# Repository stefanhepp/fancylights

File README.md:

FancyLights
===========

This is the sourcecode and plans for my home LED light and projector control system.

Content
=======

This project consists of the following controller boards:
- `keypad`: Sources for a keypad controller that communicates via RS232 with the main controller board and via I2C with a Raspberry PI.
- `fancycontrol`: Sources for the main light controller, which controls the lights and screen, and communicates via I2C with the projector control board.
- `projector`: Sources for the projector control board, which controls a servo for the projector mount locking mechanism and communicates via RS232 with the projector.

This repository contains the following folders:
- `kicad`: KiCAD schematics for all boards.
- `src`: Sources for all AtMega microcontrollers.

License
=======

This program is free software: you can redistribute it and/or modify
it under the terms of the GNU General Public License as published by
the Free Software Foundation, either version 3 of the License, or
(at your option) any later version.

This program is distributed in the hope that it will be useful,
but WITHOUT ANY WARRANTY; without even the implied warranty of
MERCHANTABILITY or FITNESS FOR A PARTICULAR PURPOSE.  See the
GNU General Public License for more details.

You should have received a copy of the GNU General Public License
along with this program.  If not, see <https://www.gnu.org/licenses/>.

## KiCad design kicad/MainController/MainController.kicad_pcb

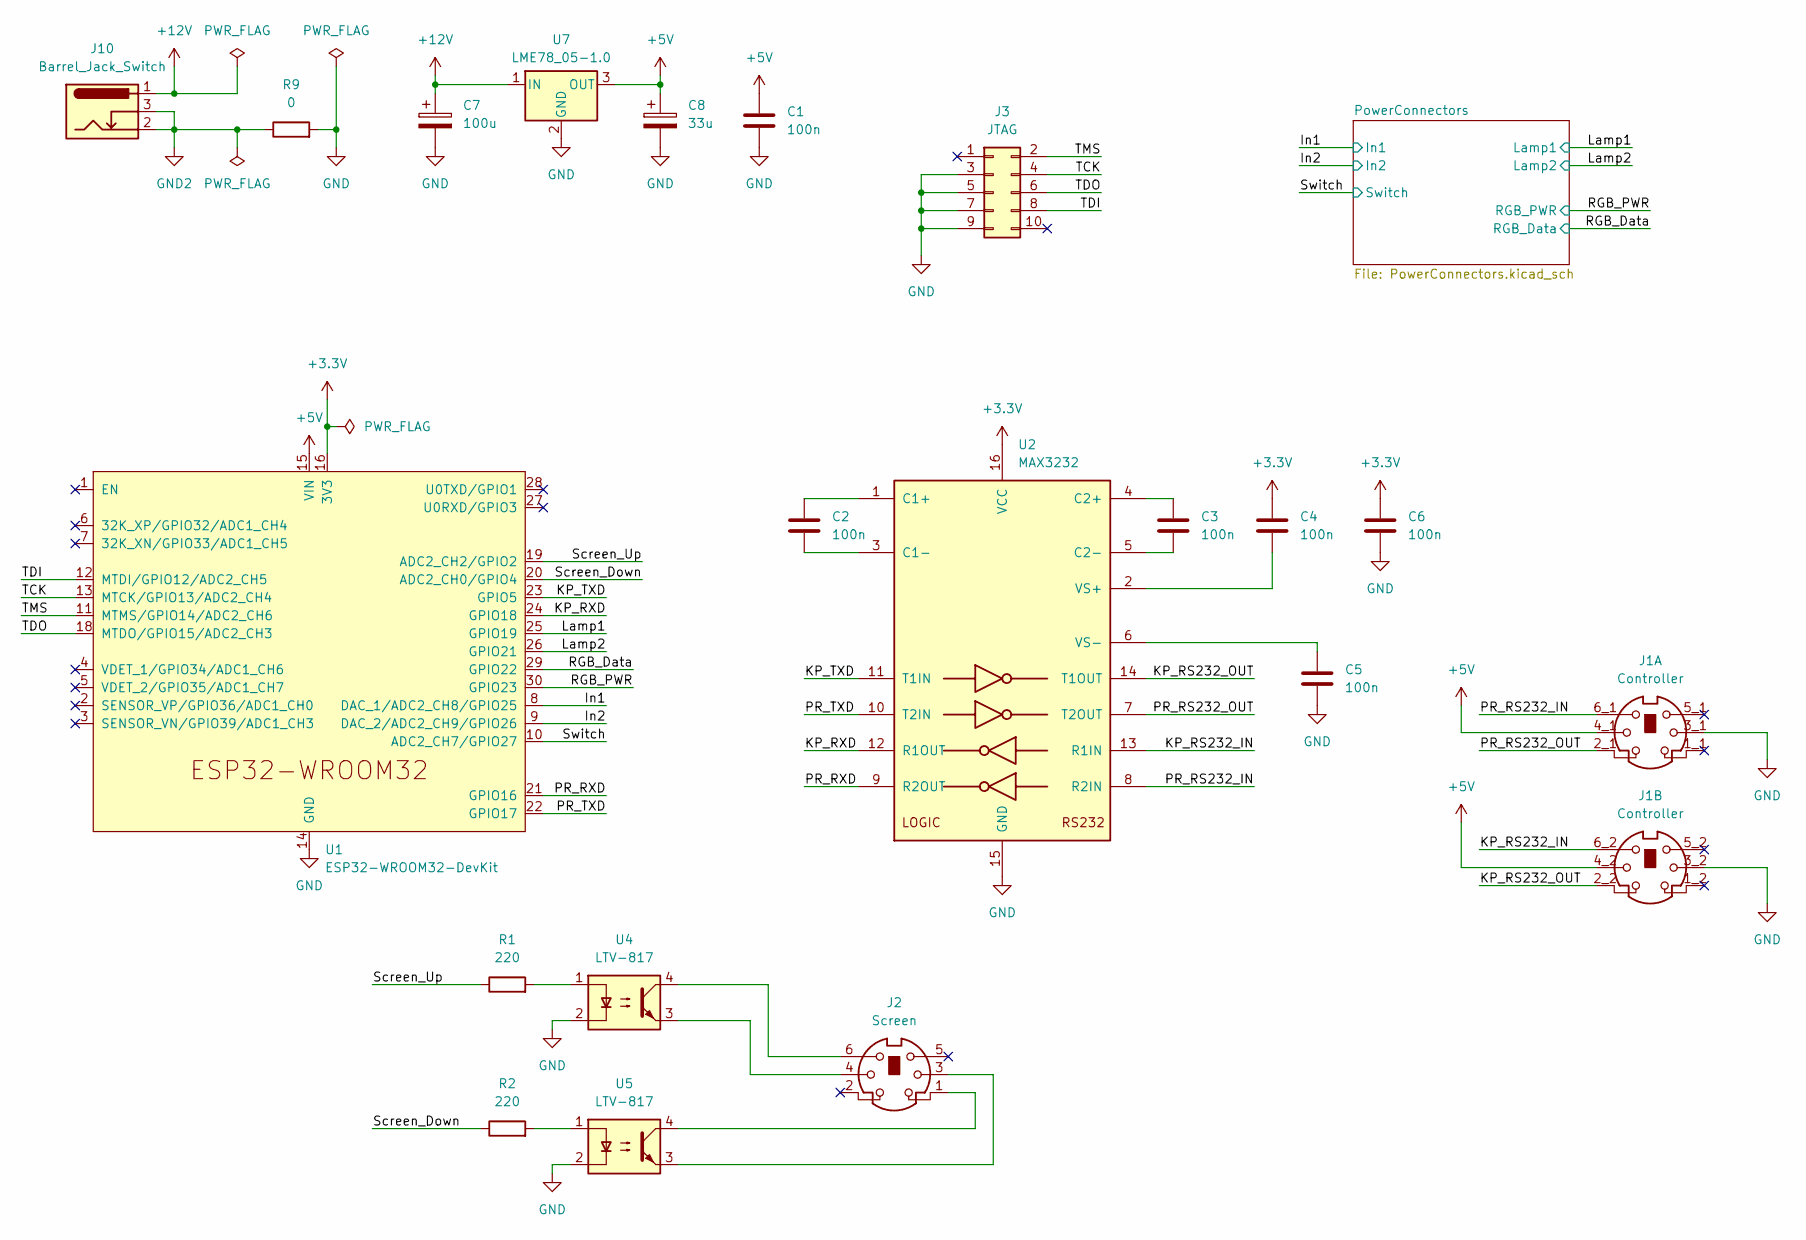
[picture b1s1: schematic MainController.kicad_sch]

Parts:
C1, C2, C3, C4, C5, C6: 100n; C_Disc_D3.4mm_W2.1mm_P2.50mm
C7: 100u; CP_Radial_D7.5mm_P2.50mm
C8: 33u; CP_Radial_D5.0mm_P2.50mm
J1: Controller; SWITCHCRAFT_DMD6FRA111
J2: Screen; MiniDIN TE_5749180-1
J3: JTAG; IDC-Header_2x05_P2.54mm_Vertical
J10: Barrel_Jack_Switch; BarrelJack_Horizontal
R1, R2: 220; R_Axial_DIN0207_L6.3mm_D2.5mm_P10.16mm_Horizontal
R9: 0; R_Axial_DIN0207_L6.3mm_D2.5mm_P10.16mm_Horizontal
U1: ESP32-WROOM32-DevKit; ESP32-WROOM32-DevKit_NoMountingHoles
U2: MAX3232; SOIC-16_3.9x9.9mm_P1.27mm
U4, U5: LTV-817; DIP-4_W7.62mm
U7: LME78_05-1.0; Converter_DCDC_GAPTEC_LME78_05-1.0

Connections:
+3.3V: C4.2, C6.1, U1.16 (3V3), U2.16 (VCC)
+5V: C1.1, C8.1, J1.4_1, J1.4_2, U1.15 (VIN), U7.3 (OUT); also elsewhere on the board
+12V: C7.1, J10.1, U7.1 (IN); also elsewhere on the board
/In1: U1.8 (DAC_1/ADC2_CH8/GPIO25); also elsewhere on the board
/In2: U1.9 (DAC_2/ADC2_CH9/GPIO26); also elsewhere on the board
/KP_RS232_IN: J1.6_2, U2.13 (R1IN)
/KP_RS232_OUT: J1.2_2, U2.14 (T1OUT)
/KP_RXD: U1.24 (GPIO18), U2.12 (R1OUT)
/KP_TXD: U1.23 (GPIO5), U2.11 (T1IN)
/Lamp1: U1.25 (GPIO19); also elsewhere on the board
/Lamp2: U1.26 (GPIO21); also elsewhere on the board
/PR_RS232_IN: J1.6_1, U2.8 (R2IN)
/PR_RS232_OUT: J1.2_1, U2.7 (T2OUT)
/PR_RXD: U1.21 (GPIO16), U2.9 (R2OUT)
/PR_TXD: U1.22 (GPIO17), U2.10 (T2IN)
/RGB_Data: U1.29 (GPIO22); also elsewhere on the board
/RGB_PWR: U1.30 (GPIO23); also elsewhere on the board
/Screen_Down: R2.1, U1.20 (ADC2_CH0/GPIO4)
/Screen_Up: R1.1, U1.19 (ADC2_CH2/GPIO2)
/Switch: U1.10 (ADC2_CH7/GPIO27); also elsewhere on the board
/TCK: J3.4, U1.13 (MTCK/GPIO13/ADC2_CH4)
/TDI: J3.8, U1.12 (MTDI/GPIO12/ADC2_CH5)
/TDO: J3.6, U1.18 (MTDO/GPIO15/ADC2_CH3)
/TMS: J3.2, U1.11 (MTMS/GPIO14/ADC2_CH6)
GND: C1.2, C5.2, C6.2, C7.2, C8.2, J1.3_1, J1.3_2, J3.3, J3.5, J3.7, J3.9, R9.2, U1.14 (GND), U1.17 (GND), U2.15 (GND), U4.2, U5.2, U7.2 (GND); also elsewhere on the board
GND2: J10.2, J10.3, R9.1; also elsewhere on the board
unnamed: J2.1, U5.4
unnamed: J2.3, U5.3
unnamed: J2.4, U4.3
unnamed: J2.6, U4.4
unnamed: R1.2, U4.1
unnamed: R2.2, U5.1
unnamed: C2.1, U2.1 (C1+)
unnamed: C2.2, U2.3 (C1-)
unnamed: C3.1, U2.4 (C2+)
unnamed: C3.2, U2.5 (C2-)
unnamed: C4.1, U2.2 (VS+)
unnamed: C5.1, U2.6 (VS-)

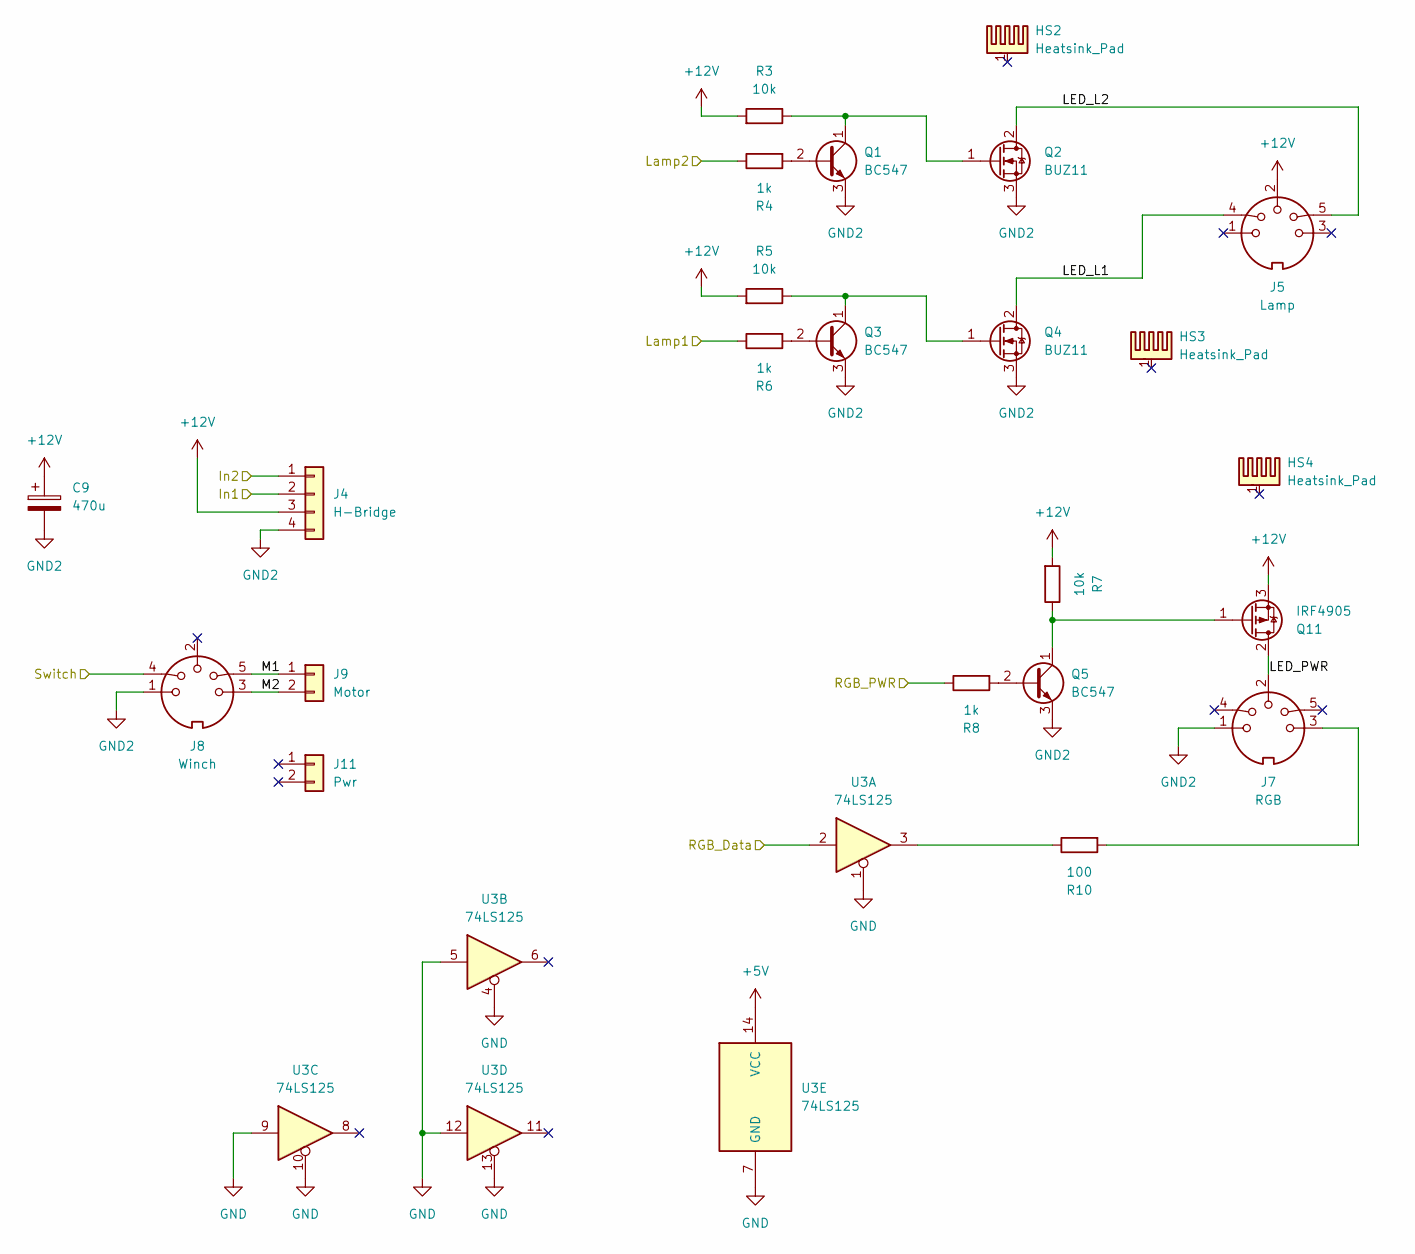
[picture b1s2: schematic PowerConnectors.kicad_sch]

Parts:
C9: 470u; CP_Radial_D10.0mm_P5.00mm
HS2, HS3, HS4: Heatsink_Pad; Heatsink_Aavid_TO-220_H12.7mm
J4: H-Bridge; PinHeader_1x04_P2.54mm_Vertical
J5: Lamp; DIN-5 MAB5P
J7: RGB; DIN-5 MAB5P
J8: Winch; DIN-5 MAB5P
J9: Motor; PinHeader_1x02_P2.54mm_Vertical
J11: Pwr; PinHeader_1x02_P2.54mm_Vertical
Q1, Q3, Q5: BC547; TO-92_Milling
Q2, Q4: BUZ11; TO-220-3_Vertical
Q11: IRF4905; TO-220-3_Vertical
R3, R5: 10k; R_Axial_DIN0207_L6.3mm_D2.5mm_P2.54mm_Vertical
R4, R6, R8: 1k; R_Axial_DIN0207_L6.3mm_D2.5mm_P10.16mm_Horizontal
R7: 10k; R_Axial_DIN0207_L6.3mm_D2.5mm_P10.16mm_Horizontal
R10: 100; R_Axial_DIN0207_L6.3mm_D2.5mm_P10.16mm_Horizontal
U3: 74LS125; DIP-14_W7.62mm

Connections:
+5V: U3.14 (VCC); also elsewhere on the board
+12V: C9.1, J4.3, J5.2, Q11.3 (S), R3.2, R5.2, R7.2; also elsewhere on the board
/In1: J4.2; also elsewhere on the board
/In2: J4.1; also elsewhere on the board
/Lamp1: R6.1; also elsewhere on the board
/Lamp2: R4.1; also elsewhere on the board
/PowerConnectors/LED_L1: J5.4, Q4.2 (D)
/PowerConnectors/LED_L2: J5.5, Q2.2 (D)
/PowerConnectors/LED_PWR: J7.2, Q11.2 (D)
/PowerConnectors/M1: J8.5, J9.1
/PowerConnectors/M2: J8.3, J9.2
/RGB_Data: U3.2; also elsewhere on the board
/RGB_PWR: R8.1; also elsewhere on the board
/Switch: J8.4; also elsewhere on the board
GND: U3.1, U3.4, U3.5, U3.7 (GND), U3.9, U3.10, U3.12, U3.13; also elsewhere on the board
GND2: C9.2, J4.4, J7.1, J8.1, Q1.3 (E), Q2.3 (S), Q3.3 (E), Q4.3 (S), Q5.3 (E); also elsewhere on the board
unnamed: J7.3, R10.2
unnamed: Q1.2 (B), R4.2
unnamed: Q1.1 (C), Q2.1 (G), R3.1
unnamed: Q3.2 (B), R6.2
unnamed: Q3.1 (C), Q4.1 (G), R5.1
unnamed: Q5.2 (B), R8.2
unnamed: Q5.1 (C), Q11.1 (G), R7.1
unnamed: R10.1, U3.3

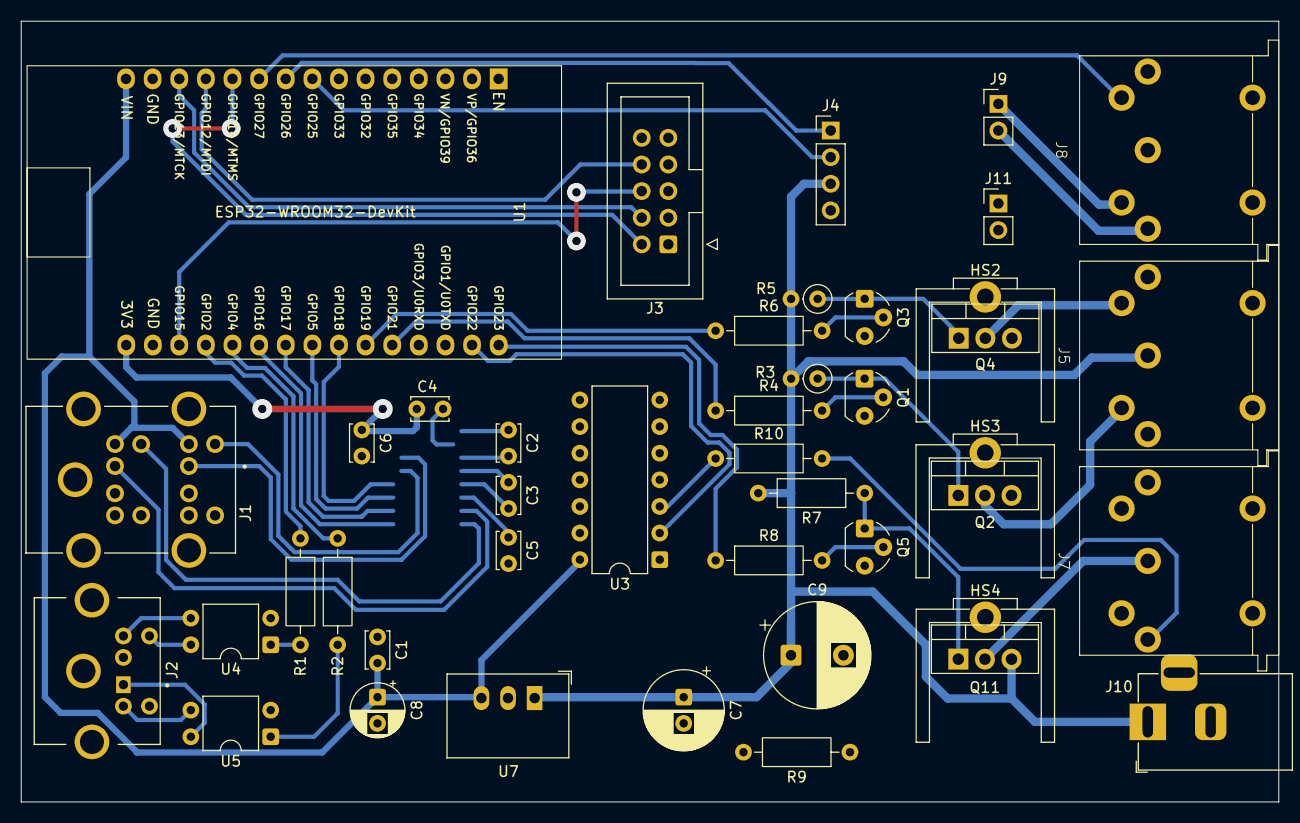
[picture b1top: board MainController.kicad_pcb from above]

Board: 2 copper layers, 120.0 x 74.5 mm, 44 parts (1 on the bottom side), 51 nets.

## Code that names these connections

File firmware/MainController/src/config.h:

/*
 * @project     FancyLights
 * @author      Stefan Hepp, stefan@stefant.org
 *
 * common custom IO and config settings.
 *
 * Copyright (c) 2024 Stefan Hepp
 * License: GPL v3
 * See 'COPYRIGHT.txt' for copyright and licensing information.
 */
#pragma once

#include <Arduino.h>

/* ==================================================== */
/* Common controller settings                           */
/* ==================================================== */

static const uint8_t PIN_RGB_DATA     = 22;
static const uint8_t PIN_RGB_PWR      = 23;
static const uint8_t PIN_LAMP1        = 19;
static const uint8_t PIN_LAMP2        = 21;
static const uint8_t PIN_SCREEN_UP    = 4;
static const uint8_t PIN_SCREEN_DOWN  = 2;
static const uint8_t PIN_WINCH_SWITCH = 27;
static const uint8_t PIN_MOTOR_IN1    = 25;
static const uint8_t PIN_MOTOR_IN2    = 26;

static const uint8_t UART_KEYPAD      = 1;
static const uint8_t UART_PROJECTOR   = 2;

static const uint8_t PIN_KP_TXD       = 5;
static const uint8_t PIN_KP_RXD       = 18;
static const uint8_t PIN_PR_TXD       = 17;
static const uint8_t PIN_PR_RXD       = 16;

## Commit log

2021-05-08 Initial makefile and sources
2022-06-08 Renamed project to FancyLights
2024-02-27 Added Boards connections draw.io file
2024-03-29 Added keypad schematics
2024-03-29 Fixed keypad wiring schematics
2024-03-31 Added schematics for projector controller, initial source project
2024-04-01 Complete schematics, using UART for communications
2024-11-06 Initial platformio projects
2024-11-19 Added interrupt for Raspberry PI I2C
2024-11-22 Changed RS232 pin mapping
2024-11-25 Implementation of keypad controller
2024-11-25 Implemented keypad commands
2024-11-25 Fixes for keypad implementation
2024-11-26 Initial implementatoin of light controller
2024-11-28 Initial implementation of color conversions and basic light modes
2024-11-28 Bugfixes for UART protocol
2024-11-28 Bugfixes for LED outputs
2024-11-29 Using HSV values instead of RGB, using HSV-to-RGB implementation from Stultiens.
2024-11-30 Fix HSV h value scaling
2024-12-02 Implemented screen up/down and adjust RGB intensity
2024-12-05 More coarse steps for keypad HSV controls
2025-04-10 Initial schematic for ESP32 based LED controller
2025-04-23 New main controller PCB layout using ESP32
2025-04-24 Updated main controller implementation for ESP32
2025-05-08 Added debug target for ESP32
2025-05-23 Updated main controller for digital RGB strip
2025-05-26 Fixed footprints for MainController board
2025-06-07 Added commandline interface to main controller
2025-06-19 Using FastLED to control RGB strips
2025-06-19 Fixes for Commandline parser
2025-06-21 Fixes for LED intensity, added LED command
2025-06-21 Fixed MainController LED power and data drivers
2025-06-28 Added some MQTT client implementation
2025-06-30 Initial MqttBroker class
2025-07-01 Fixes for wifi and mqtt commands
2025-07-02 Cleanup to PCB layout
2025-07-08 First full implementation of MQTT client
2025-07-08 Fixed Mqtt client implementation
2025-07-11 Implemented LED effects
2025-07-12 Fixed the animations
2025-07-12 Fix for screen up/down pulse
2025-07-14 Fixed screen up/down pin assignment
2026-01-07 Send MQTT updates to keypad, read projector power status
2026-04-08 Fixed fade animation, added 'light' MQTT topic
2026-04-09 Added projector commands
2026-04-09 Fixed fade effect
2026-04-19 Removed old AtMega main controller implememtation
2026-04-22 Remove old controller folder from workspace
2026-04-25 Fixed projector controls
